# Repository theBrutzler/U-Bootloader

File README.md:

# U-Bootloader

Learnin PCB with many Sensors. Made in Twitchstream. SUB Tember board!

I created a board!

with interesting backside XD

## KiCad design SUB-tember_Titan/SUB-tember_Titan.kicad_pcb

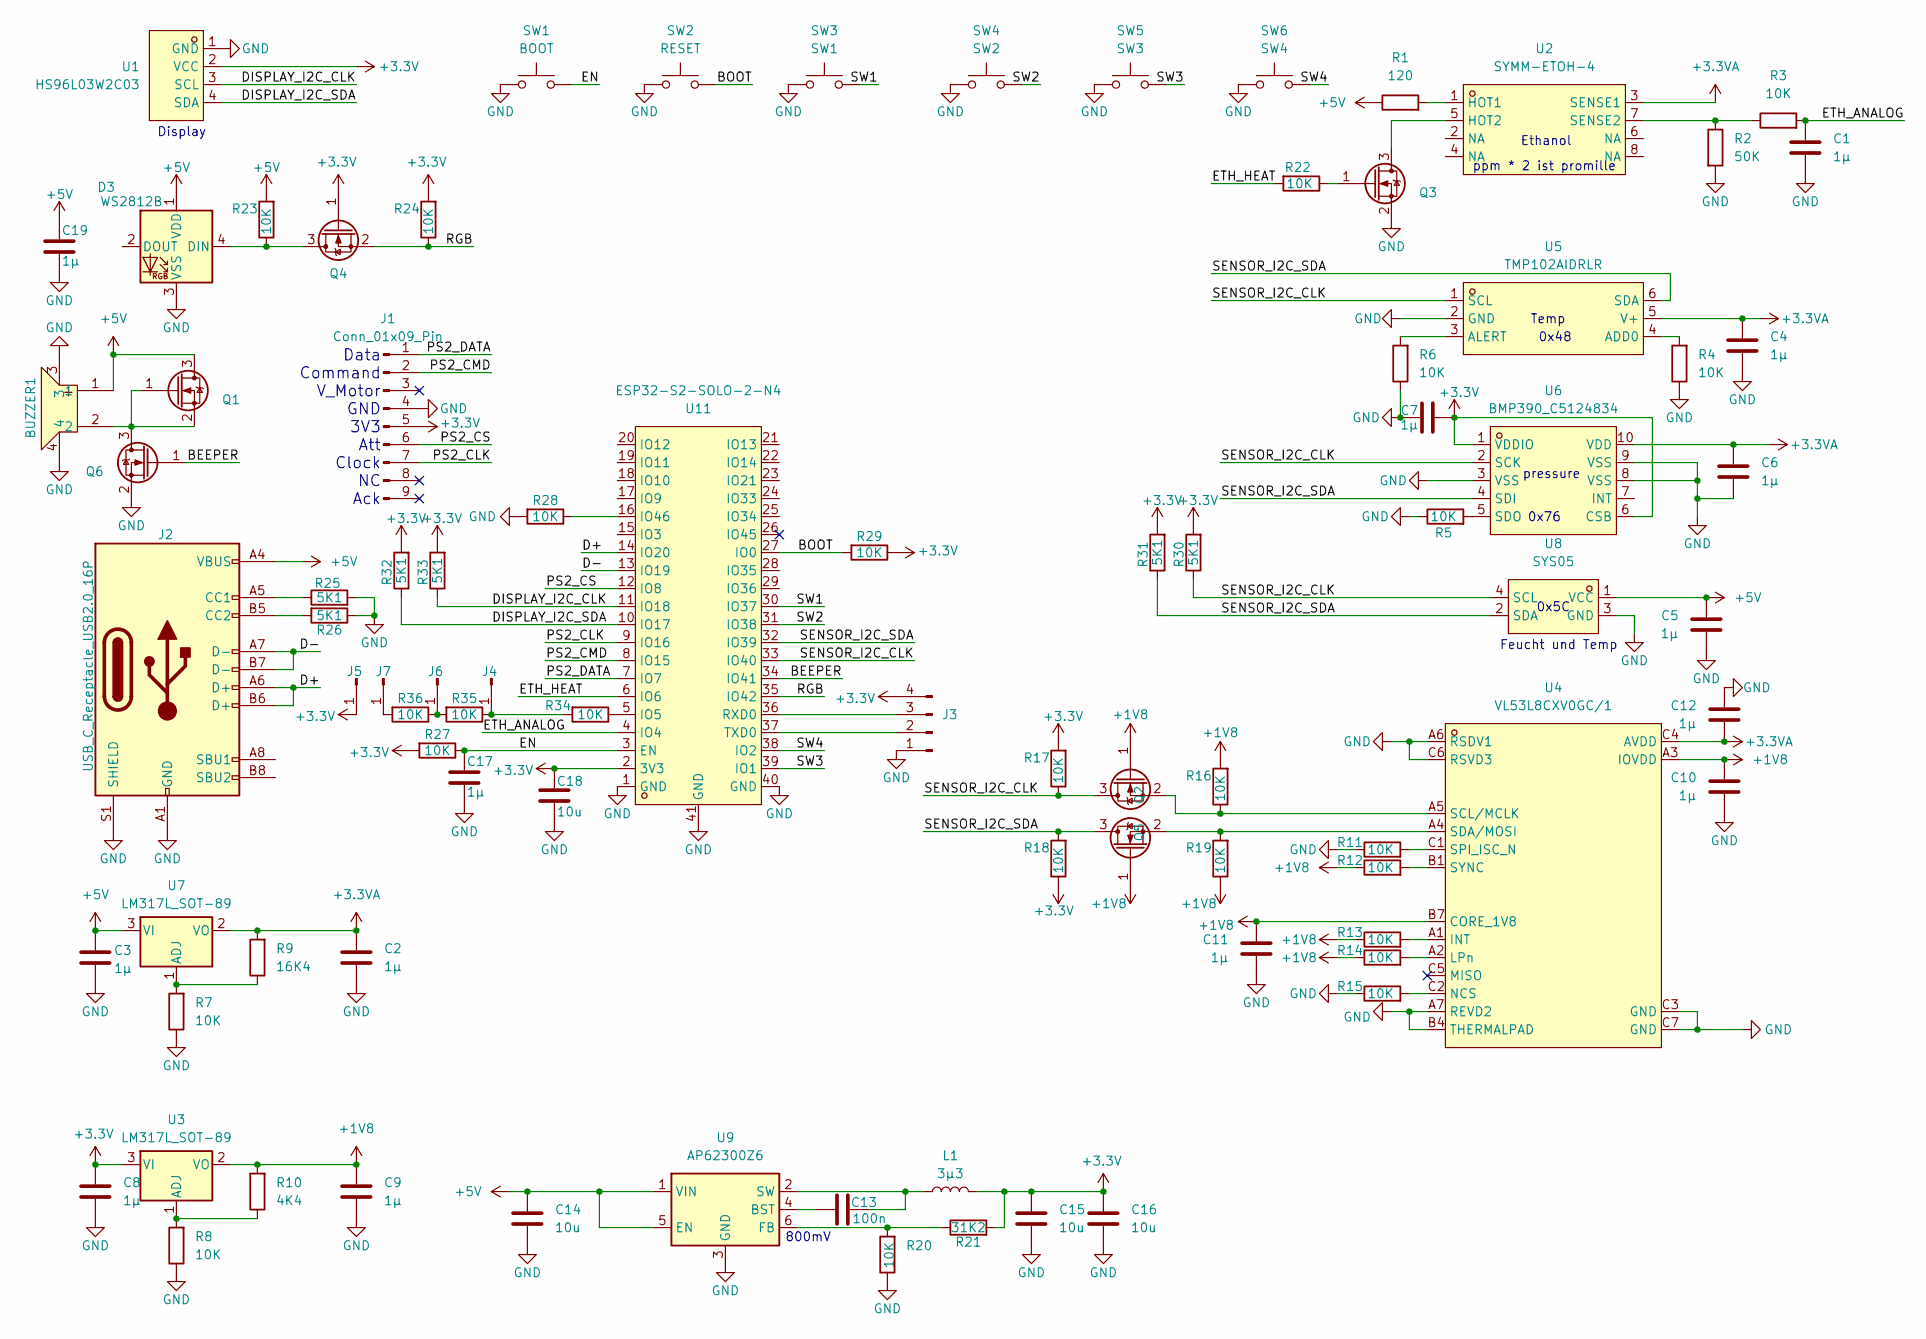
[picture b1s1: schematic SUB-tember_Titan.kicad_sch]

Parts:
BUZZER1: SMD7525-16Ω; BUZ-SMD_4P-L7.5-W7.5-BR; LCSC Part C49246950
C1, C2, C3, C4, C5, C6, C7, C8, C9, C10, C11, C12, C17, C19: 1µ; C_0603_1608Metric; LCSC Part C6119849
C13: 100n; C_0603_1608Metric; LCSC Part C5137636
C14, C15, C16, C18: 10u; C_0603_1608Metric; LCSC Part C6119842
D3: WS2812B; LED_WS2812B_PLCC4_5.0x5.0mm_P3.2mm; LCSC Part C22461793
J1: Conn_01x09_Pin; PinHeader_1x09_P2.54mm_Vertical
J2: USB_C_Receptacle_USB2.0_16P; USB_C_Receptacle_GCT_USB4105-xx-A_16P_TopMnt_Horizontal; LCSC Part C2927038
J3: Conn_01x04_Pin; PinHeader_1x04_P2.54mm_Vertical
J4, J5, J6, J7: Conn_01x01_Pin; PinHeader_1x01_P2.54mm_Vertical
L1: 3µ3; L_1210_3225Metric; LCSC Part C39846655
Q1, Q2, Q3, Q4, Q5, Q6: Q_NMOS_Depletion_GSD; SOT-23-3; LCSC Part C347475
R1: 120; R_0402_1005Metric; LCSC Part C2909315
R2: 50K; R_0402_1005Metric; LCSC Part C107229
R3, R4, R5, R6, R7, R8, R11, R12, R13, R14, R15, R16, R17, R18, R19, R20, R22, R23, R24, R27, R28, R29, R34, R35, R36: 10K; R_0402_1005Metric; LCSC Part C3017497
R9: 16K4; R_0402_1005Metric; LCSC Part C852558
R10: 4K4; R_0402_1005Metric; LCSC Part C321517
R21: 31K2; R_0402_1005Metric; LCSC Part C2088574
R25, R26, R30, R31, R32, R33: 5K1; R_0402_1005Metric; LCSC Part C2906948
SW1: BOOT; SW_SPST_EVQP7C
SW2: RESET; SW_SPST_EVQP7C
SW3: SW1; SW_SPST_EVQP7C
SW4: SW2; SW_SPST_EVQP7C
SW5: SW3; SW_SPST_EVQP7C
SW6: SW4; SW_SPST_EVQP7C
U1: HS96L03W2C03; OLED-TH_L27.8-W27.2-P2.54_C9900033791; LCSC Part C5248080
U2: SYMM-ETOH-4; LCC-8_L3.8-W3.8-P1.27-BL; LCSC Part C22363926
U3, U7: LM317L_SOT-89; SOT-89-3; LCSC Part C45953613
U4: VL53L8CXV0GC/1; LGA-16_L6.4-W3.0_VL53L5CXV0GC-1; LCSC Part C7386355
U5: TMP102AIDRLR; SOT-563_L1.6-W1.2-P0.50-LS1.6-BR; LCSC Part C99269
U6: BMP390_C5124834; LGA-10_L2.0-W2.0-P0.50-BL; LCSC Part C5124834
U8: SYS05; SIP-4_L12.0-W5.5-P2.54-L; LCSC Part C19727297
U9: AP62300Z6; SOT-563; LCSC Part C5250745
U11: ESP32-S2-SOLO-2-N4; WIRELM-SMD_ESP32-S3-WROOM-1; LCSC Part C3040594

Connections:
+1V8: C9.1, C10.1, C11.1, Q2.1 (G), Q5.1 (G), R10.2, R12.1, R13.1, R14.1, R16.2, R19.1, U3.2 (VO), U4.A3 (IOVDD), U4.B7 (CORE_1V8)
+3.3V: C7.2, C8.1, C15.1, C16.1, C18.1, J1.5, J3.4, J5.1, L1.2, Q4.1 (G), R17.2, R18.1, R21.2, R24.2, R27.2, R29.1, R30.2, R31.2, R32.2, R33.2, U1.2 (VCC), U3.3 (VI), U6.1 (VDDIO), U6.6 (CSB), U11.2 (3V3)
+3.3VA: C2.1, C4.1, C6.1, C12.2, R9.2, U2.3 (SENSE1), U4.C4 (AVDD), U5.5 (V+), U6.10 (VDD), U7.2 (VO)
+5V: BUZZER1.1, C3.1, C5.1, C14.1, C19.1, D3.1 (VDD), J2.A4 (VBUS), J2.A9 (VBUS), J2.B4 (VBUS), J2.B9 (VBUS), Q1.3 (D), R1.1, R23.2, U7.3 (VI), U8.1 (VCC), U9.1 (VIN), U9.5 (EN)
/BEEPER: Q6.1 (G), U11.34 (IO41)
/BOOT: R29.2, SW2.2, U11.27 (IO0)
/D+: J2.A6 (D+), J2.B6 (D+), U11.14 (IO20)
/D-: J2.A7 (D-), J2.B7 (D-), U11.13 (IO19)
/DISPLAY_I2C_CLK: R33.1, U1.3 (SCL), U11.11 (IO18)
/DISPLAY_I2C_SDA: R32.1, U1.4 (SDA), U11.10 (IO17)
/EN: C17.1, R27.1, SW1.2, U11.3 (EN)
/ETH_ANALOG: C1.1, R3.2, U11.4 (IO4)
/ETH_HEAT: R22.2, U11.6 (IO6)
/PS2_CLK: J1.7, U11.9 (IO16)
/PS2_CMD: J1.2, U11.8 (IO15)
/PS2_CS: J1.6, U11.12 (IO8)
/PS2_DATA: J1.1, U11.7 (IO7)
/RGB: Q4.2 (S), R24.1, U11.35 (IO42)
/SENSOR_I2C_CLK: Q5.3 (D), R17.1, R30.1, U5.1 (SCL), U6.2 (SCK), U8.4 (SCL), U11.33 (IO40)
/SENSOR_I2C_SDA: Q2.3 (D), R18.2, R31.1, U5.6 (SDA), U6.4 (SDI), U8.2 (SDA), U11.32 (IO39)
/SW1: SW3.2, U11.30 (IO37)
/SW2: SW4.2, U11.31 (IO38)
/SW3: SW5.2, U11.39 (IO1)
/SW4: SW6.2, U11.38 (IO2)
GND: BUZZER1.3, BUZZER1.4, C1.2, C2.2, C3.2, C4.2, C5.2, C6.2, C7.1, C8.2, C9.2, C10.2, C11.2, C12.1, C14.2, C15.2, C16.2, C17.2, C18.2, C19.2, D3.3 (VSS), J1.4, J2.A1 (GND), J2.A12 (GND), J2.B1 (GND), J2.B12 (GND), J2.S1 (SHIELD), J3.1, Q3.2 (S), Q6.2 (S), R2.2, R4.1, R5.1, R6.1, R7.1, R8.1, R11.1, R15.1, R20.1, R25.2, R26.1, R28.2, SW1.1, SW2.1, SW3.1, SW4.1, SW5.1, SW6.1, U1.1 (GND), U4.A6 (RSDV1), U4.A7 (REVD2), U4.B4 (THERMALPAD), U4.C3 (GND), U4.C6 (RSVD3), U4.C7 (GND), U5.2 (GND), U6.3 (VSS), U6.8 (VSS), U6.9 (VSS), U8.3 (GND), U9.3 (GND), U11.1 (GND), U11.40 (GND), U11.41 (GND)
unnamed: D3.4 (DIN), Q4.3 (D), R23.1
unnamed: J2.A5 (CC1), R25.1
unnamed: J2.B5 (CC2), R26.2
unnamed: J3.2, U11.37 (TXD0)
unnamed: J3.3, U11.36 (RXD0)
unnamed: J4.1, R34.2, R35.1
unnamed: J6.1, R35.2, R36.1
unnamed: J7.1, R36.2
unnamed: BUZZER1.2, Q1.1 (G), Q1.2 (S), Q6.3 (D)
unnamed: Q2.2 (S), R19.2, U4.A4 (SDA/MOSI)
unnamed: Q3.3 (D), U2.5 (HOT2)
unnamed: Q3.1 (G), R22.1
unnamed: Q5.2 (S), R16.1, U4.A5 (SCL/MCLK)
unnamed: R1.2, U2.1 (HOT1)
unnamed: R2.1, R3.1, U2.7 (SENSE2)
unnamed: R8.2, R10.1, U3.1 (ADJ)
unnamed: R13.2, U4.A1 (INT)
unnamed: R14.2, U4.A2 (LPn)
unnamed: R15.2, U4.C2 (NCS)
unnamed: R11.2, U4.C1 (SPI_ISC_N)
unnamed: R12.2, U4.B1 (SYNC)
unnamed: R4.2, U5.4 (ADD0)
unnamed: R6.2, U5.3 (ALERT)
unnamed: R5.2, U6.5 (SDO)
unnamed: R7.2, R9.1, U7.1 (ADJ)
unnamed: C13.1, U9.4 (BST)
unnamed: R20.2, R21.1, U9.6 (FB)
unnamed: C13.2, L1.1, U9.2 (SW)
unnamed: R34.1, U11.5 (IO5)
unnamed: R28.1, U11.16 (IO46)

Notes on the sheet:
Feucht und Temp
Data Command V_Motor GND 3V3 Att Clock NC Ack
Display
800mV
0x76
Ethanol
pressure
Temp
0x48
0x5C
ppm * 2 ist promille

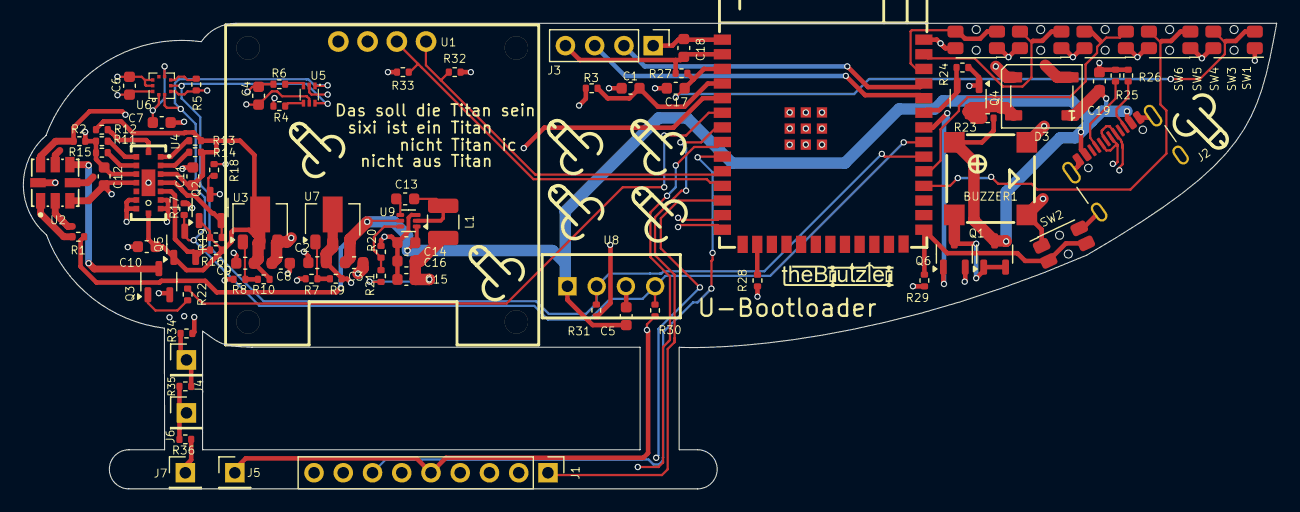
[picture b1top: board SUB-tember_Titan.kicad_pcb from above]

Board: 4 copper layers, 108.9 x 40.4 mm, 87 parts (0 on the bottom side), 55 nets.

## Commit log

2025-09-09 inital upload
2025-09-11 update inital software build UNTESTED!!!
2025-09-25 update software and html bom
2025-09-29 Ein paar extra Penoiden
2025-10-16 add dorRied_initial
